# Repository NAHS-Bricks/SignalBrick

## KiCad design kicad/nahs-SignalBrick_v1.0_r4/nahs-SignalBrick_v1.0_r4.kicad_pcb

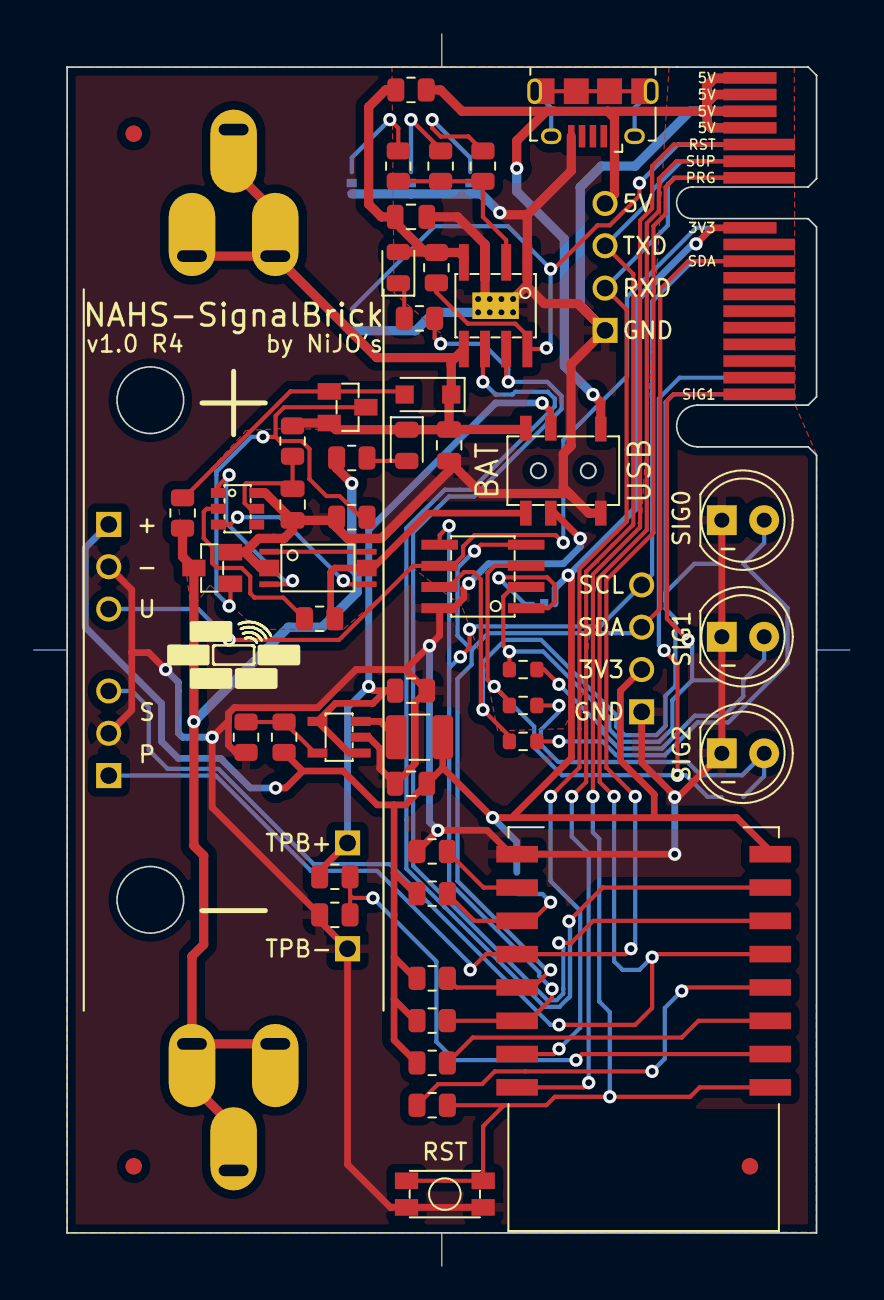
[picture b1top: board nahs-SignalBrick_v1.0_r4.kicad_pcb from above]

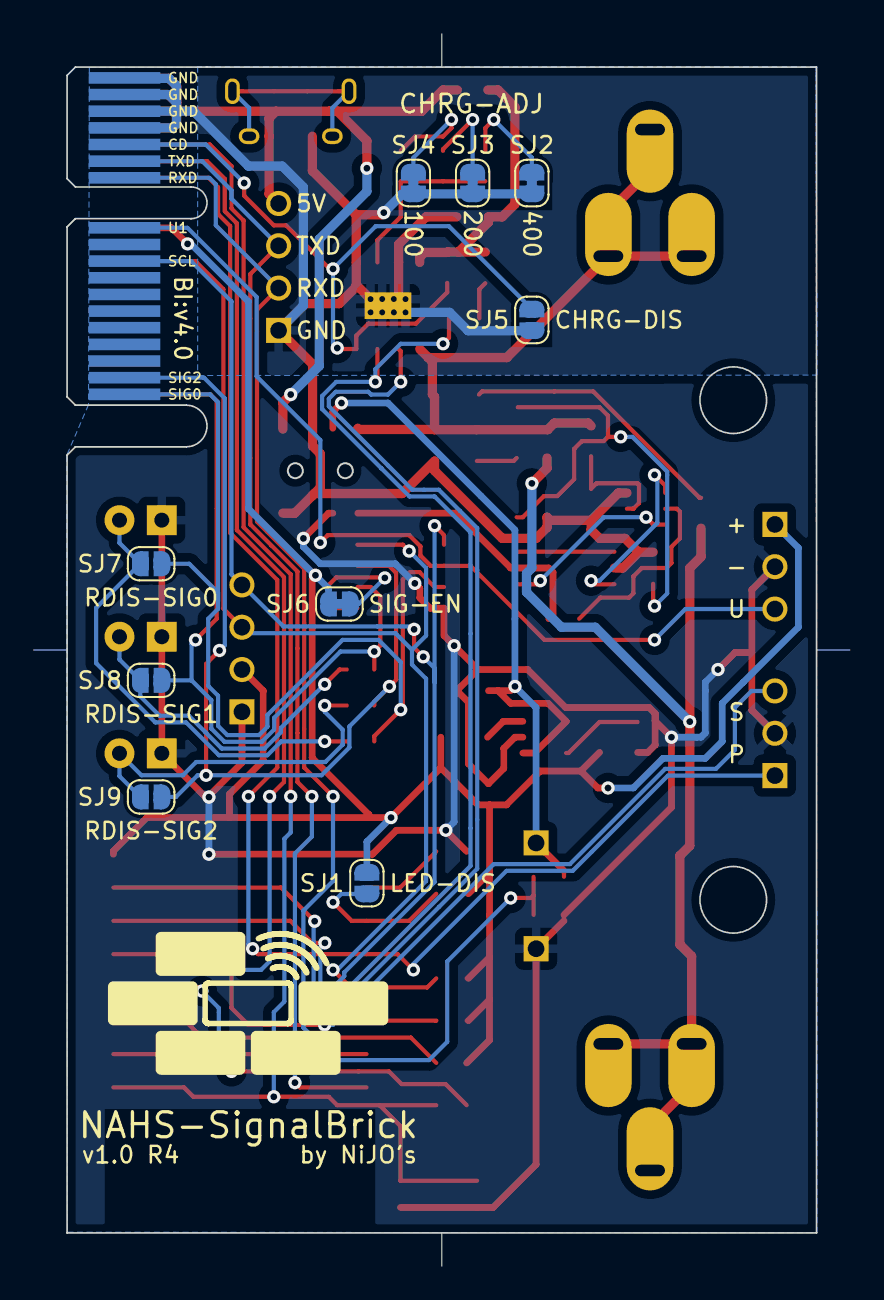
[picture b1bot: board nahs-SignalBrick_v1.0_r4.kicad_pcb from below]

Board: 2 copper layers, 48.9 x 73.9 mm, 69 parts (10 on the bottom side), 47 nets.

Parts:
BT: HA_18650_EK
C1, C1#2, C1#3, C1#4, C1#5: 100nF; C_0805_2012Metric
D1: 1N4148WL; D_SOD-123F
FID1, FID2, FID3: Fiducial; Fiducial_1mm_Mask2mm
IC1: ESP12S
IC?: ATTINY212; SOIC8
J: Brick-Interface-V4; Brick_Interface_V4_inset
J2: USB_B_Mini; USB_Micro-B_Amphenol_10118194_Horizontal
JP1, JP5: PINHD_1X03; PINHD_1X03_2.54_1mm_Round
JP1#2: RHT-ALT; PINHD_1X04_2.54_1mm_Round
JP2: PINHD_1X04; PINHD_1X04_2.54_1mm_Round
JP3, JP4: PINHD_1X01; PINHD_1X01_2.54_1mm_Square
L1: 2.2µH; L_1210_3225Metric
LED1: Green; LED_0805_2012Metric
LED2: Red; LED_0805_2012Metric
LED3: SIG0; LED_D5.0mm
LED4: SIG1; LED_D5.0mm
LED5: SIG2; LED_D5.0mm
LOGO1: brick_logo; x8mm
LOGO2: brick_logo; x17mm
Q1: 8205A; TSSOP8_MS
Q3: CJ2302; SOT23
Q4: MMBT2907A; SOT23
R1, R16, R24: 330; R_0603_1608Metric
R2, R11, R14, R17: 1k; R_0805_2012Metric
R3, R4, R7, R13, R18, R19: 10k; R_0805_2012Metric
R5, R6: 3.9k; R_0805_2012Metric
R8: 2.7M; R_0805_2012Metric
R9, R21: 590k; R_0805_2012Metric
R10: 100; R_0805_2012Metric
R12: 0.4; R_0805_2012Metric
R15: 3k; R_0805_2012Metric
R20: 130k; R_0805_2012Metric
R22: 6,04k; R_0805_2012Metric
R23: 12k; R_0805_2012Metric
SJ1, SJ1#3, SJ1#5: RHT-ALT; SolderJumper-2_P1.3mm_Bridged_RoundedPad1.0x1.5mm
SJ1#2, SJ1#4: LED-DIS; SolderJumper-2_P1.3mm_Open_RoundedPad1.0x1.5mm
SJ6: SIG-EN; SolderJumper-2_P1.3mm_Bridged_RoundedPad1.0x1.5mm
SJ7: RDIS-SIG0; SolderJumper-2_P1.3mm_Open_RoundedPad1.0x1.5mm
SJ8: RDIS-SIG1; SolderJumper-2_P1.3mm_Open_RoundedPad1.0x1.5mm
SJ9: RDIS-SIG2; SolderJumper-2_P1.3mm_Open_RoundedPad1.0x1.5mm
SW1: KMR_231_G_LFS
SW2: SSSS820101
U1: ZD8028IB5TR; SOT23-5
U3: DW01A; SOT23-6
U4: TP4056; SOIC8_TP

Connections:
+3V3: C1#3.1, IC1.8 (VCC), J.B11 (3.3V), JP1#2.2, JP5.1, L1.2, R3.1, R4.1, R5.1, R6.1, R21.2, SJ1#4.1 (A), SJ6.1 (A)
/CHRG+: C1.1, LED1.2 (A), R12.1, R13.1, U4.4 (VCC)
A0: IC1.2 (ADC), R8.2, R9.1
BAT+: BT.P (+), C1#4.1, D1.1 (K), LED2.1 (K), Q4.2 (E), R10.2, SW2.6, U4.5 (BAT)
BAT-: BT.M (-), Q3.3 (D), R17.2, R19.1
BOOT1: IC1.17 (D4), R4.2, SJ1#4.2 (B)
BOOT2: IC1.16 (D8), R7.2
CD: J.A14 (CD), R13.2, SJ1#2.2 (B), U4.8 (CE)
CHRG: IC1.6 (D6), R14.2, U4.7 (CHRG)
EN: IC1.3 (EN), R3.2
GND: C1#2.2, C1#3.2, IC1.15 (GND), IC?.8 (GND), JP1.2, JP1#2.1, JP4.1, JP5.2, LED3.1 (K), LED4.1 (K), LED5.1 (K), R7.1, R9.2, R20.1, SW1.1, SW1.2, SW2.2, U1.2 (GND)
IN+: J.B15 (5V), J.B16 (5V), J.B17 (5V), J.B18 (5V), J2.1 (VBUS), JP2.4, R12.2, SW2.4
IN-: C1.2, C1#4.2, C1#5.2, J.A15 (GND), J.A16 (GND), J.A17 (GND), J.A18 (GND), J2.5 (GND), JP2.1, Q1.2 (S1), Q3.2 (S), R18.1, SJ1.1 (A), SJ1#2.1 (A), SJ1#3.1 (A), SJ1#5.1 (A), SW2.3, U3.6 (GND), U4.1 (TEMP), U4.3 (GND), U4.T1 (GND), U4.T2 (GND), U4.T3 (GND), U4.T4 (GND), U4.T5 (GND), U4.T6 (GND), U4.T7 (GND), U4.T8 (GND)
unnamed: C1#5.1, R10.1, U3.5 (VCC)
unnamed: D1.2 (A), Q4.1 (B), R19.2
unnamed: IC1.4 (D0), R2.1
unnamed: IC?.1 (VCC), SJ6.2 (B)
unnamed: L1.1, U1.3 (SW)
unnamed: LED1.1 (K), R14.1
unnamed: LED2.2 (A), R17.1
unnamed: LED3.2 (A), R1.2, SJ7.2 (B)
unnamed: LED4.2 (A), R16.2, SJ8.2 (B)
unnamed: LED5.2 (A), R24.2, SJ9.2 (B)
unnamed: Q1.1 (D1), Q1.6 (D2)
unnamed: Q1.3 (G1), U3.1 (OD)
unnamed: Q1.4 (G2), U3.3 (OC)
unnamed: Q3.1 (G), Q4.3 (C), R18.2
unnamed: R11.2, U3.2 (CS)
unnamed: R15.1, SJ1.2 (B)
unnamed: R15.2, R22.2, R23.2, U4.2 (PROG)
unnamed: R20.2, R21.1, U1.5 (FB)
unnamed: R22.1, SJ1#3.2 (B)
unnamed: R23.1, SJ1#5.2 (B)
PROG: IC1.18 (D3), J.B12 (PROG), JP1.1
PRT-: Q1.5 (S2), R11.1, SW2.1
RST: IC1.1 (~RST), J.B14 (RST), R2.2, SW1.3, SW1.4
RXD: IC1.21 (RXD0), J.A12 (RX), JP2.2
SCL: IC1.20 (D1), IC?.5 (PA2), J.A9 (SCL), JP1#2.4, R6.2
SDA: IC1.19 (D2), IC?.4 (PA1), J.B9 (SDA), JP1#2.3, R5.2
SEL+: C1#2.1, JP3.1, R8.1, SW2.5, U1.1 (EN), U1.4 (IN)
SETUP: IC1.5 (D5), J.B13 (SETUP), JP1.3
SIG0: IC?.7 (PA3), J.A1 (UTIL5), R1.1, SJ7.1 (A)
SIG1: IC?.2 (PA6), J.B1 (UTIL1), R16.1, SJ8.1 (A)
SIG2: IC?.3 (PA7), J.A2 (UTIL6), R24.1, SJ9.1 (A)
STDBY: IC1.7 (D7), U4.6 (STDBY)
TXD: IC1.22 (TXD0), J.A13 (TX), JP2.3
UPDI: IC?.6 (RST/UPDI), J.A11 (UPDI1), JP5.3

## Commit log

2021-02-22 Boardlayout for v1.0 R1
2021-02-22 renamed components, finished for production
2021-05-08 Boardlayout for v1.0 R2 in progress
2021-05-09 Boardlayout for v1.0 R2
2021-05-20 Boardlayout v1.0 R2 - Send to JLCPCB
2021-06-18 added platformio project for nahs-SignalBrick_v1.0
2022-01-13 build-firmware invoker
2022-02-07 Board v1.0 R3 WIP
2022-02-09 Board v1.0 R3 done
2022-02-12 Board v2.0 R1 done
2022-02-12 added ibom invoker and ibom for v2.0 r1 board
2022-11-30 changed naming of platformio project; migrated from old to new libraries in firmware
2023-01-15 Board v1.0 R4 done
